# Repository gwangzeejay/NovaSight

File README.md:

# NovaSight · Rev A P1

NovaSight là nguyên mẫu hỗ trợ người dùng gậy trắng. NovaChest đo phía trước và cảnh báo qua hai vai. NovaCane Clip gắn dưới tay cầm, có rung, đèn Xin đường và nút SOS. NovaApp là giao diện thử nghiệm tùy chọn cho Clip.

**Tài liệu chính** · [Cookbook NovaSight](COOKBOOK.md)

| Thư mục | Nội dung |
| --- | --- |
| [firmware](firmware/) | PlatformIO cho ESP32-S3 NovaChest và ESP32-C3 NovaCane Clip |
| [novaapp](novaapp/) | Ứng dụng web tĩnh tiếng Việt cho Clip qua BLE |
| [output/3d](output/3d/NovaSight-3D.html) | Lắp ráp 3D và mô phỏng sử dụng: nhân vật tóc trắng, băng mắt, áo đen tím; bối cảnh phố với cửa hàng và cây xanh |
| [hardware](hardware/) | Hai project KiCad P1, báo cáo ERC/DRC và lịch sử đi dây |
| [output/pcb-prototype](output/pcb-prototype/README.md) | Gerber, khoan và yêu cầu chế tạo bo mẫu |
| [output/pcb-review](output/pcb-review/README.md) | BOM/CPL, DXF, STEP và ghi chú kỹ thuật |
| [source_review](source_review/) | Mô tả sản phẩm, brief PCB và tài liệu tham chiếu |
| [tools](tools/) và [tests](tests/) | Kiểm tra CAD/CAM, logic firmware và giao thức NovaApp. `python -X utf8 tools/bom.py` gộp BOM P1, gán mã LCSC và kiểm tra tồn kho JLCPCB, kết quả ở `output/bom/p1` |

Chạy từ thư mục gốc sau khi đã cài PlatformIO, Python, KiCad 10 và Node.js. Nếu đường dẫn dự án có dấu tiếng Việt, `pio run` lỗi `.tmp: Invalid argument`. Đặt trước `PYTHONUTF8=1`, `PLATFORMIO_BUILD_DIR` và `PLATFORMIO_LIBDEPS_DIR` trỏ tới thư mục ASCII, như [Cookbook mục 3](COOKBOOK.md).

```powershell
pio run -d firmware
python tools/hardware.py
python tools/test_core.py
node --test tests/app_test.mjs
python -m http.server 8000 --bind 127.0.0.1 --directory novaapp
```

Mở [NovaApp trên localhost](http://localhost:8000) trong trình duyệt hỗ trợ Web Bluetooth. Cookbook có lệnh cho đường dẫn Windows chứa dấu, thứ tự cấp nguồn, nạp, hiệu chuẩn và kiểm thử trên mẫu.

Để xem mô phỏng, chạy `python -m http.server 8765 --bind 127.0.0.1` từ thư mục gốc rồi mở [NovaSight 3D](http://localhost:8765/output/3d/NovaSight-3D.html), chọn **Mô phỏng sử dụng**. Phím **5** hoặc nút **Cận cảnh nhân vật** mở góc nhìn nhân vật; **1–4** đổi các góc nhìn còn lại, **Space** chạy/dừng, **F** trình chiếu. Hình học nhân vật và bối cảnh được dựng trực tiếp trong HTML; Three.js vẫn tải qua CDN nên cần kết nối mạng khi mở lần đầu.

P1 dùng cho thử nghiệm kỹ thuật có giám sát. Hãy tiếp tục dùng gậy trắng và kỹ thuật định hướng, di chuyển (O&M). Các phép đo trên bo thật, hiệu năng phát hiện nguy cơ và độ tin cậy SOS cần được nghiệm thu trước thử nghiệm di chuyển.

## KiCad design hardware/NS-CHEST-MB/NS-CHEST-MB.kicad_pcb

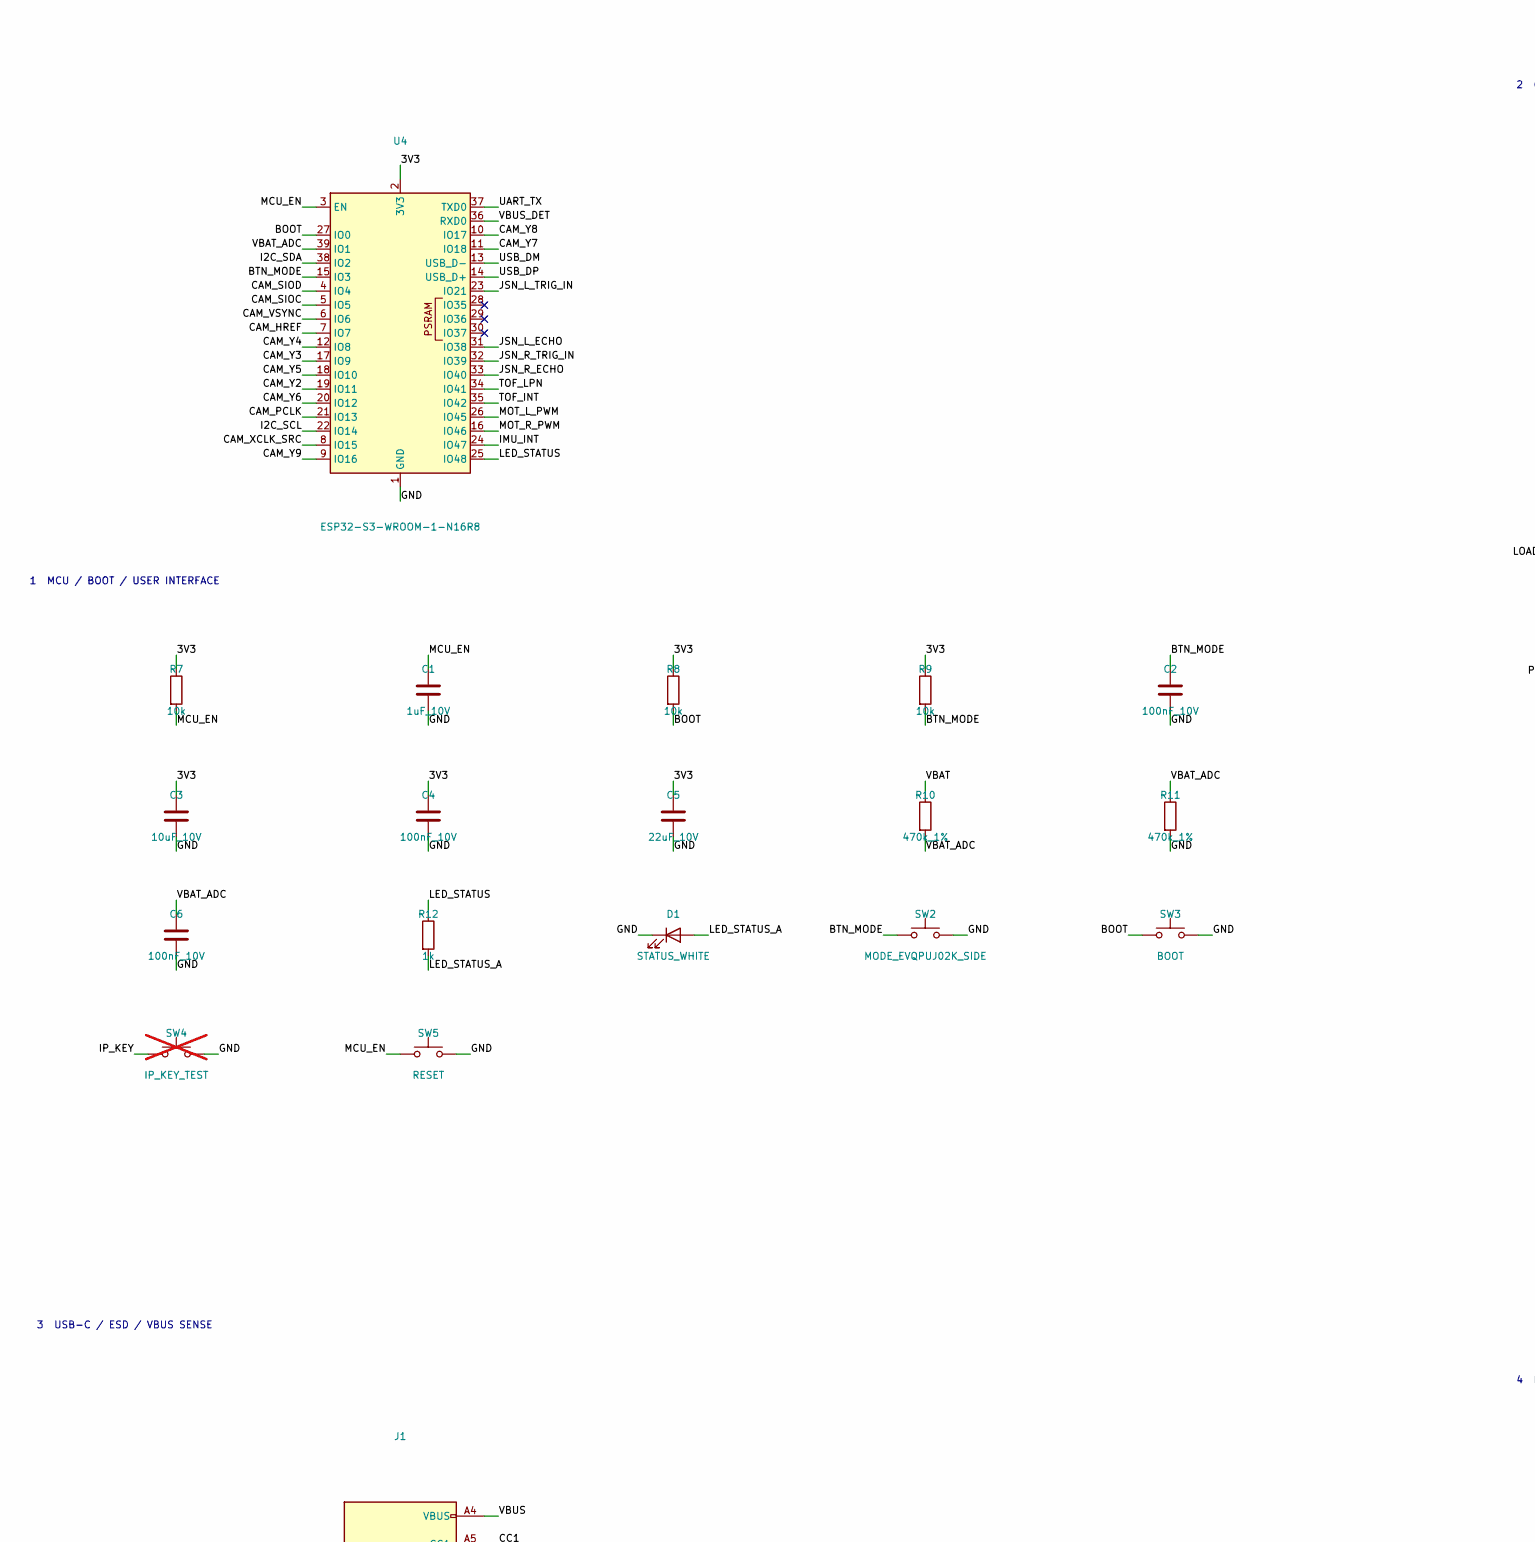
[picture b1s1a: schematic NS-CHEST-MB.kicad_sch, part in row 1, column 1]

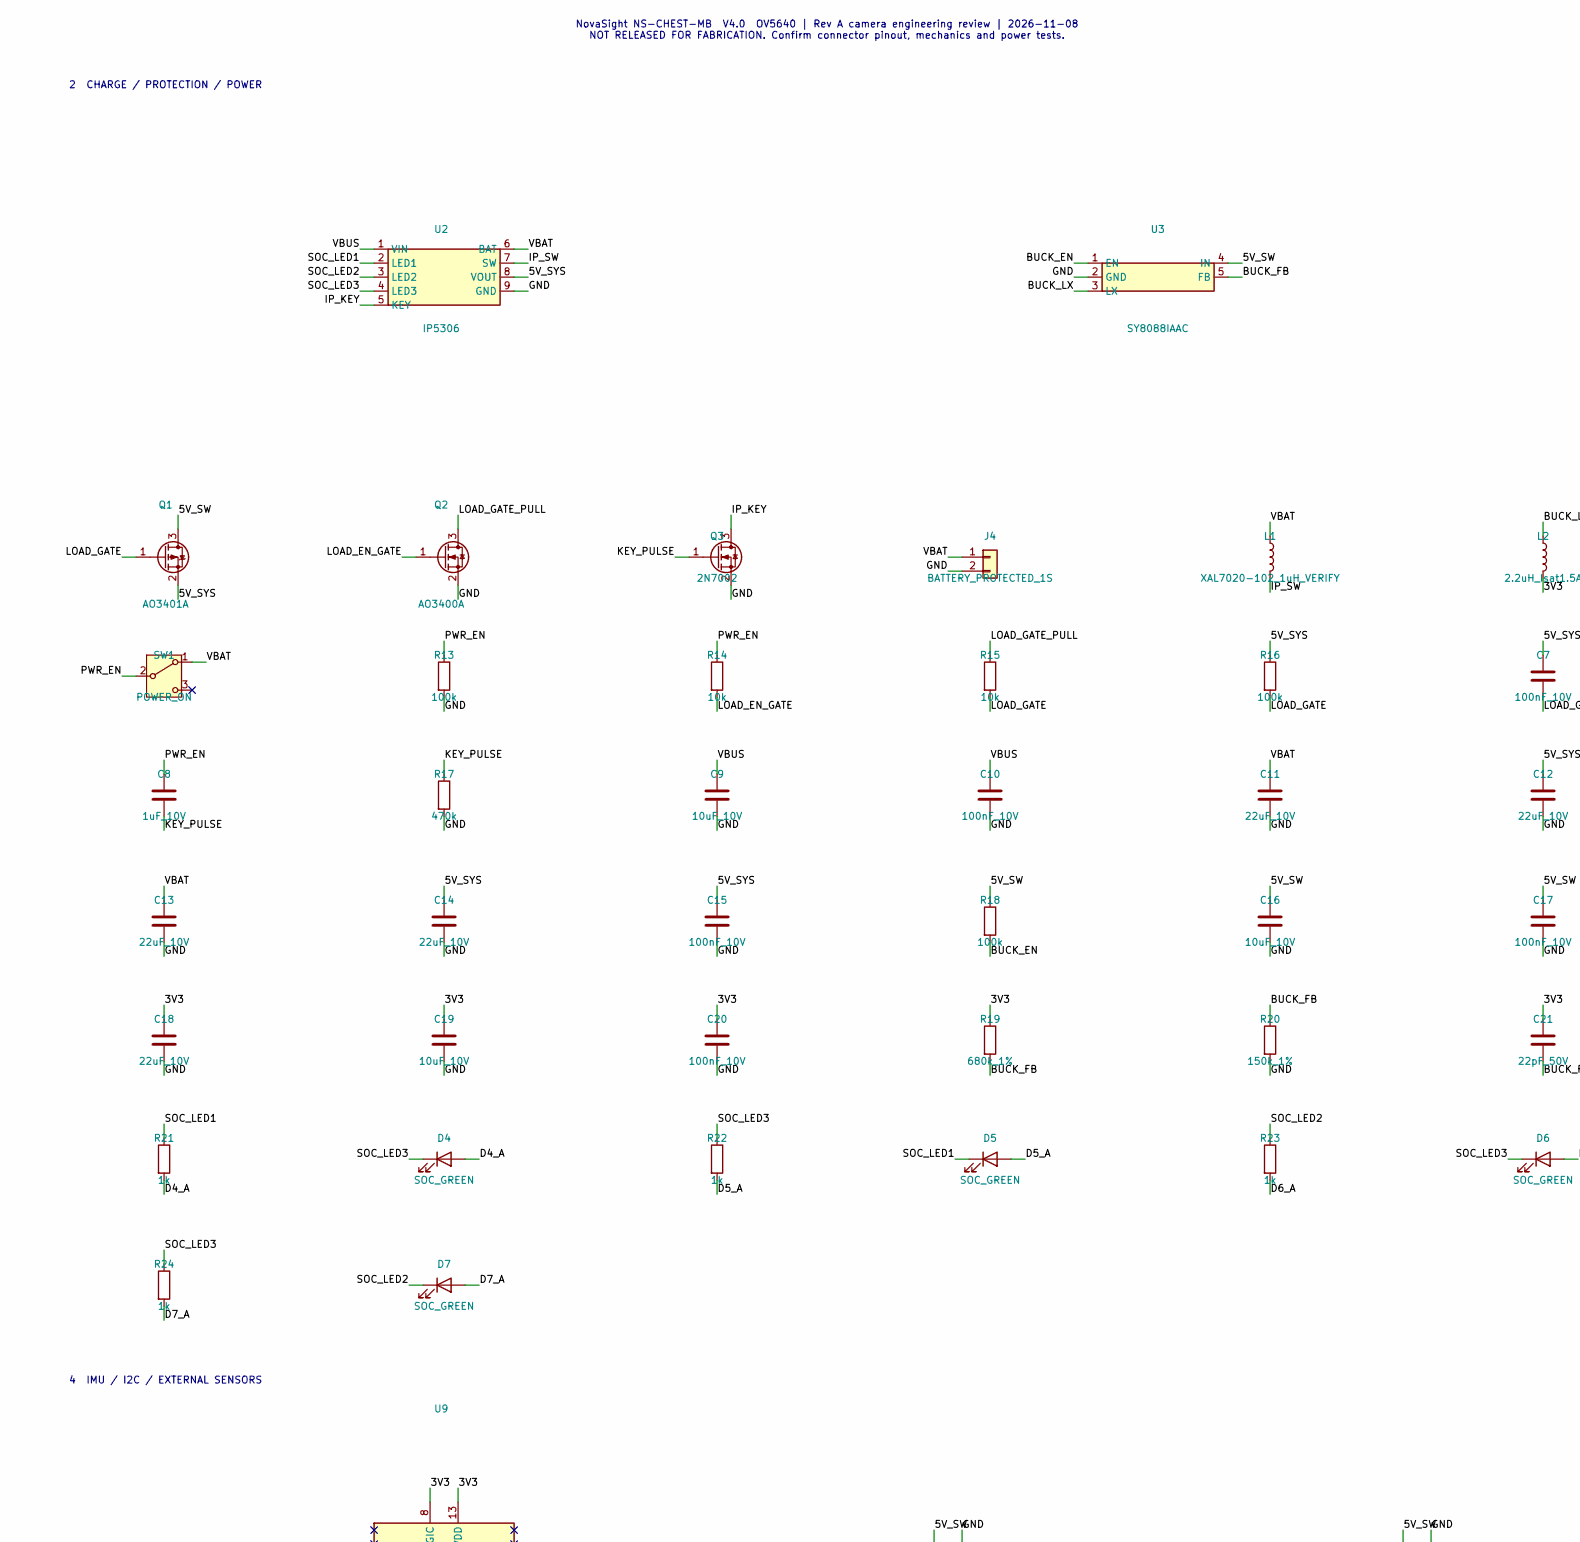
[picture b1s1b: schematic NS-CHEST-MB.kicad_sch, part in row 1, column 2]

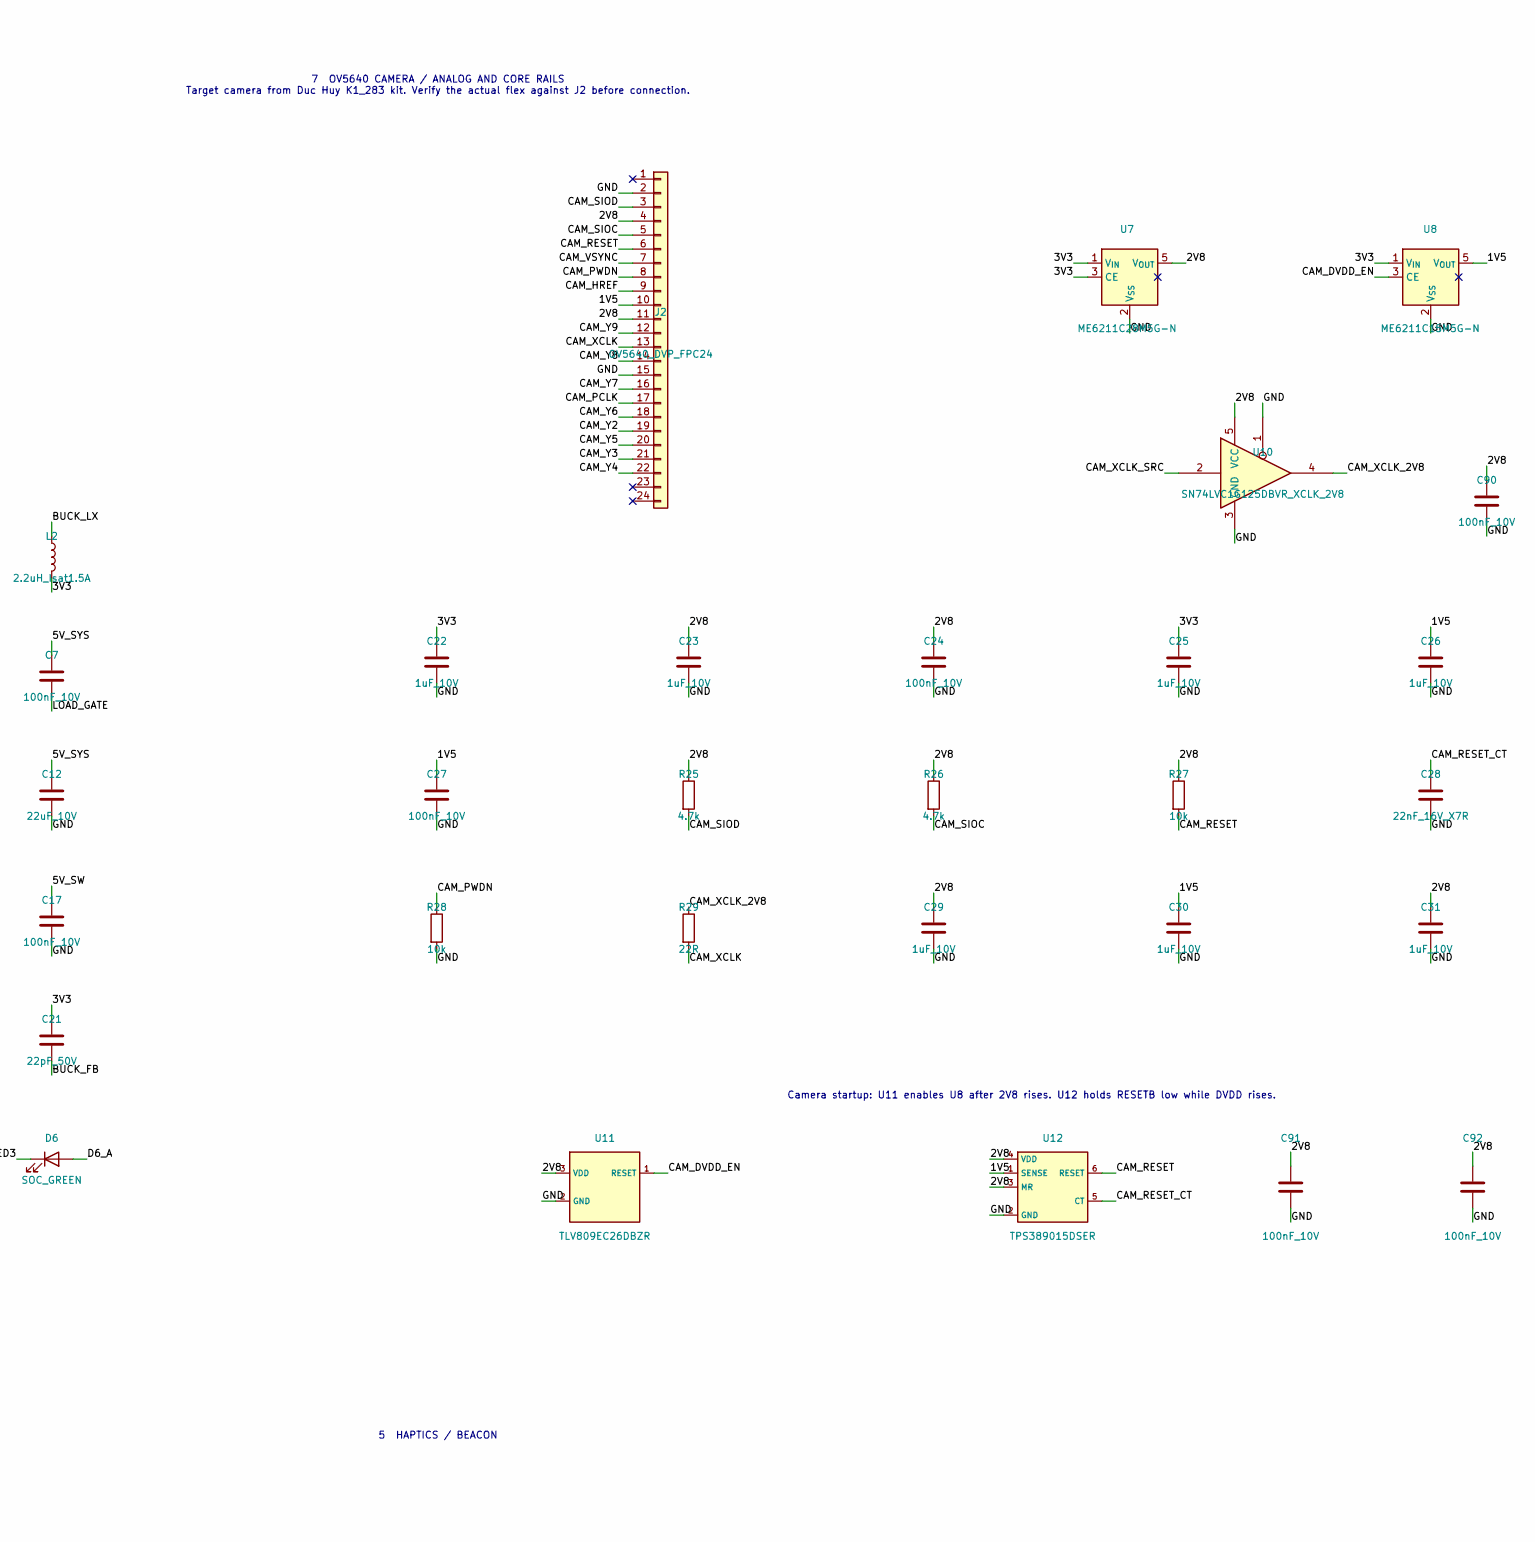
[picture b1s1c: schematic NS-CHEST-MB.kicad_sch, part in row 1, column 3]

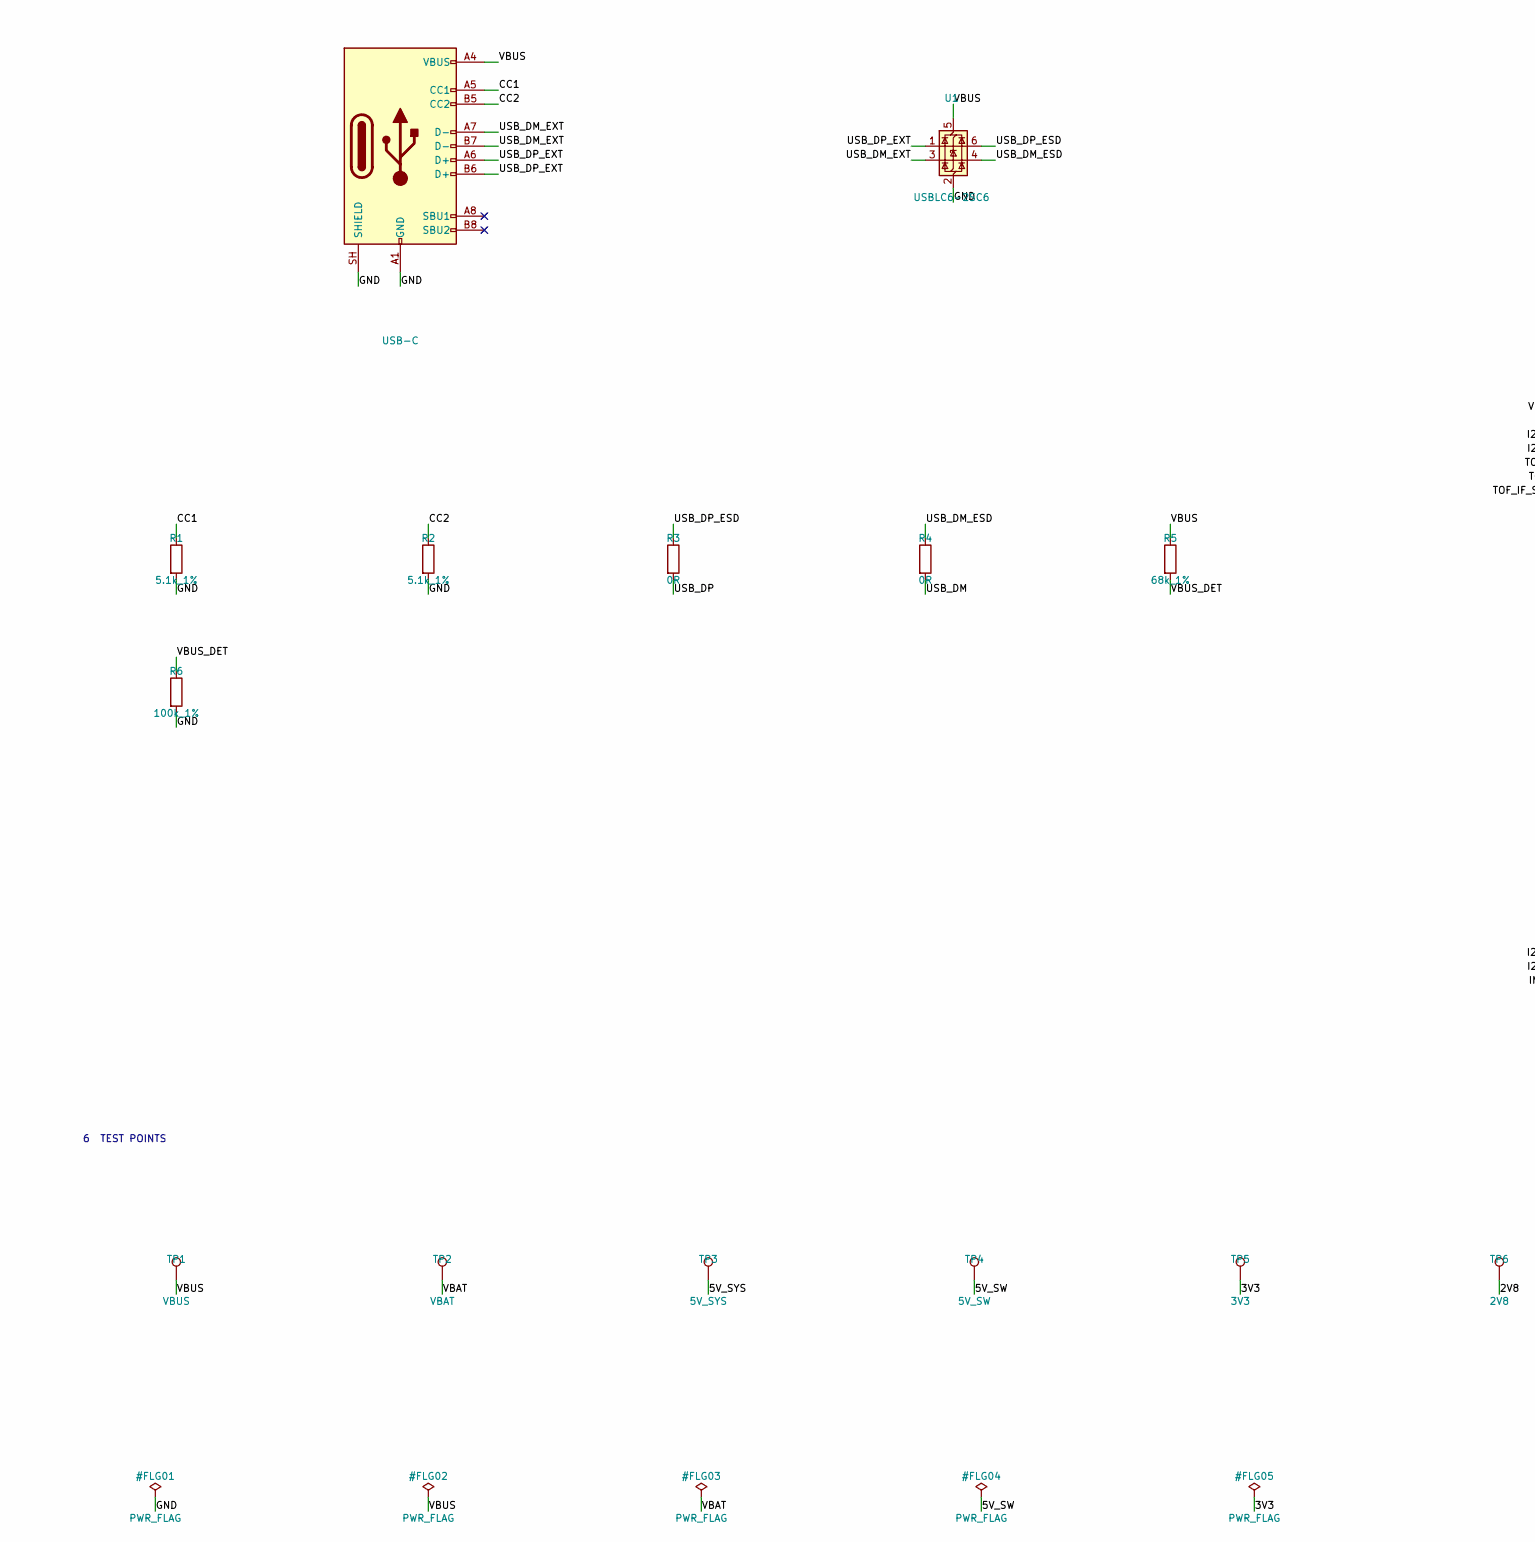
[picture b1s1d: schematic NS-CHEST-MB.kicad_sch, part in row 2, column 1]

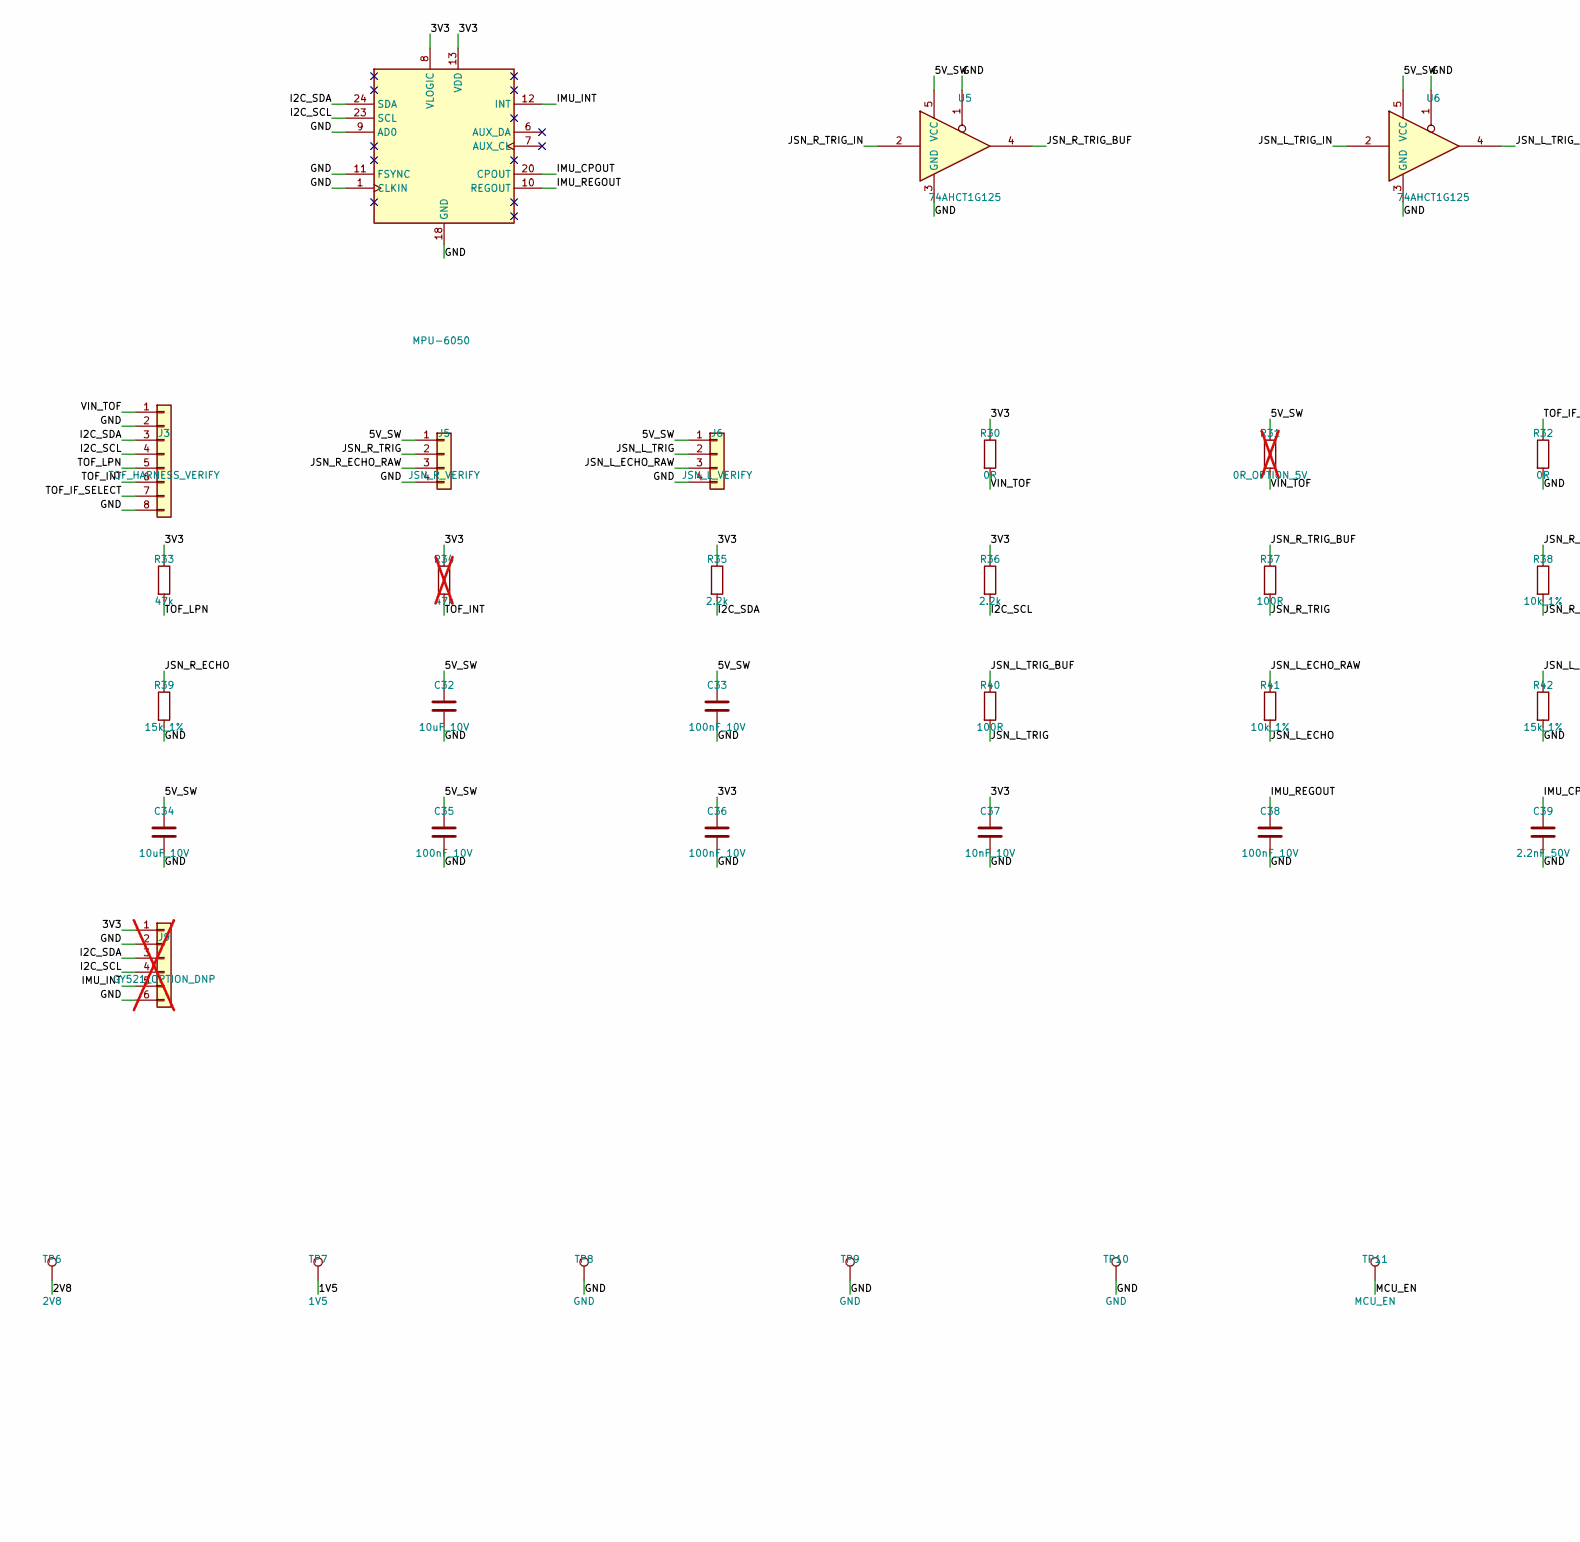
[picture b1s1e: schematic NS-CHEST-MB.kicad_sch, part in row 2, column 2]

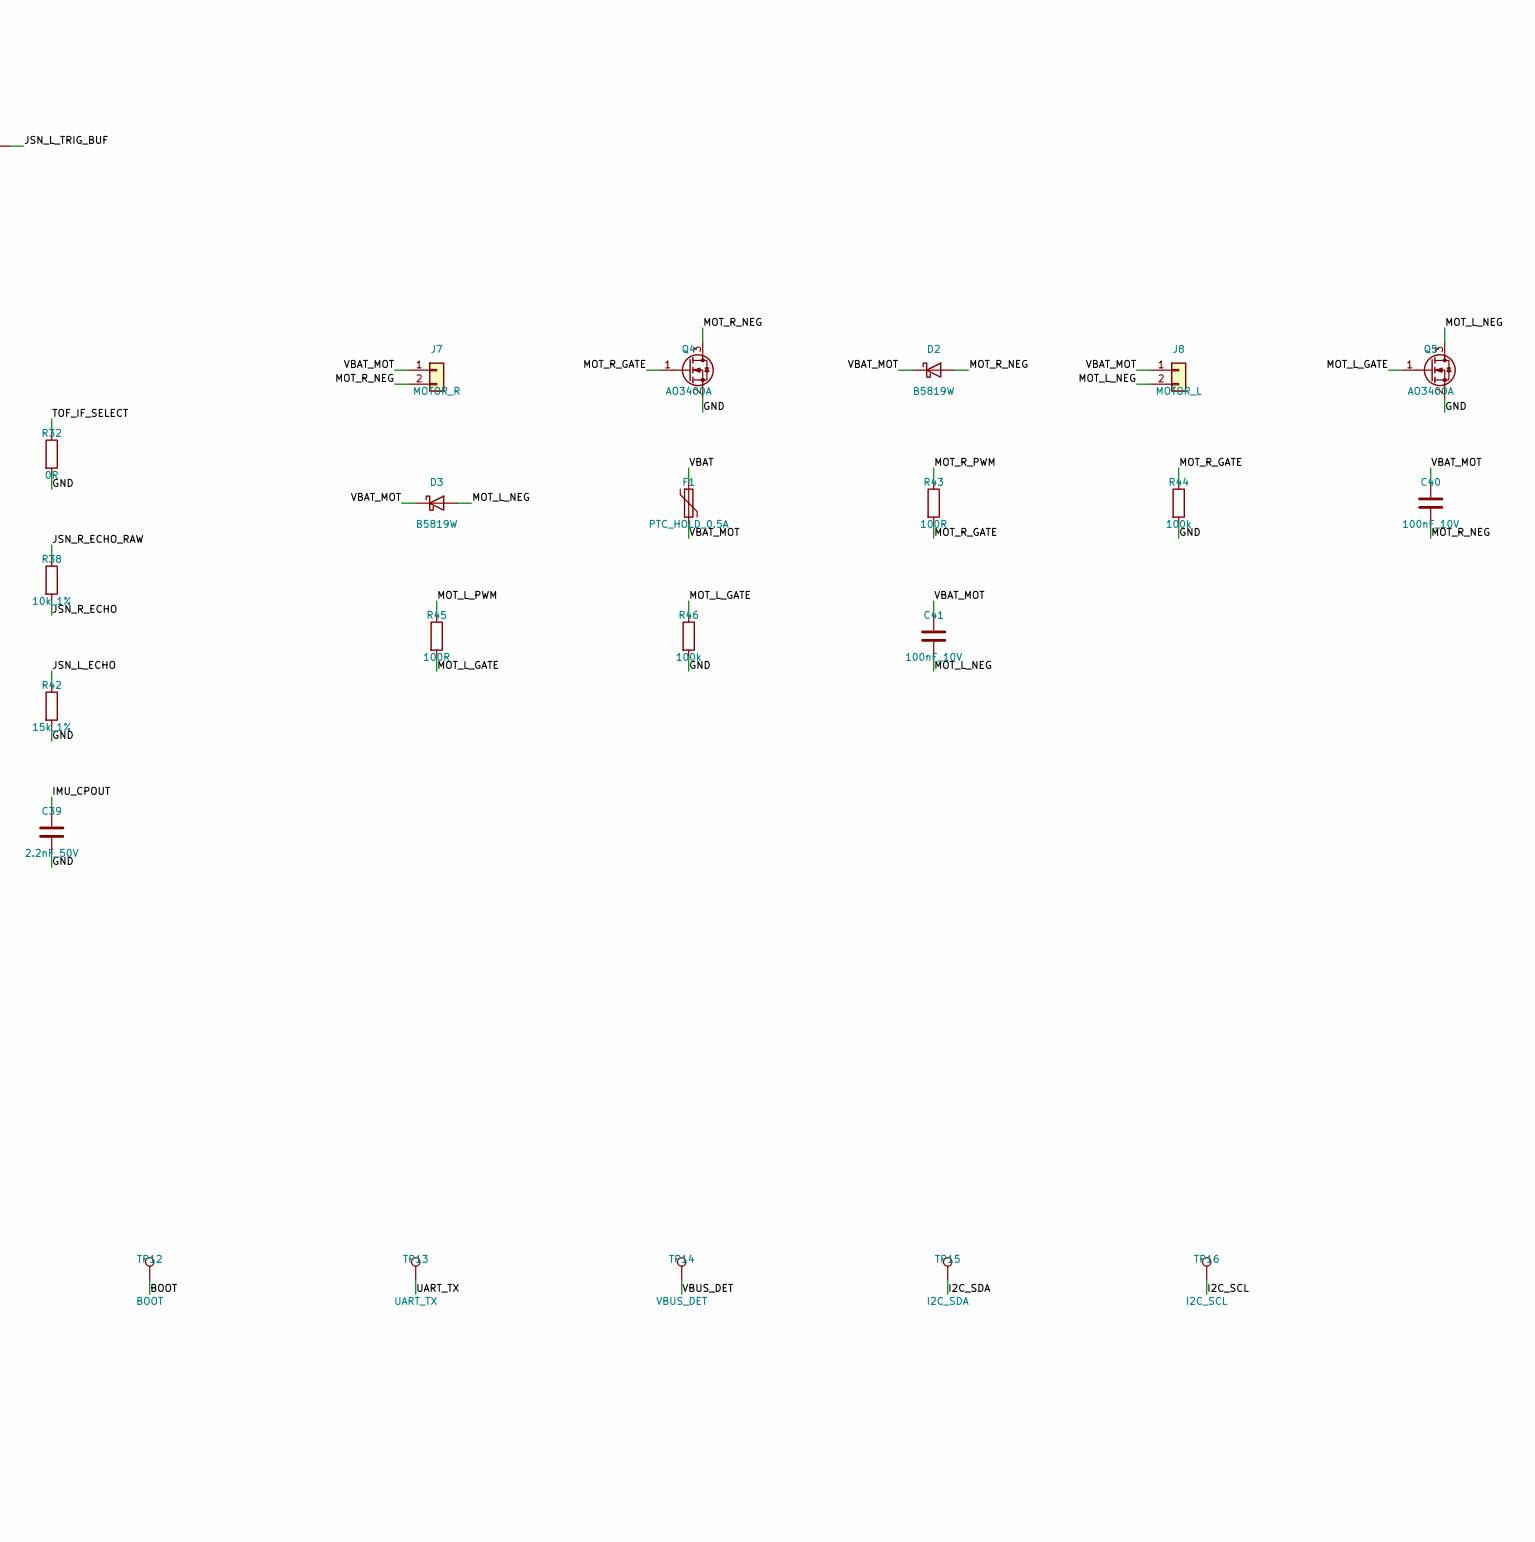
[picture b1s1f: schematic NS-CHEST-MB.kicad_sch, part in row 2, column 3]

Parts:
C1, C8, C22, C23, C25, C26, C29, C30, C31: 1uF_10V; C_0402_1005Metric
C2, C4, C6, C7, C10, C15, C17, C20, C24, C27, C33, C35, C36, C38, C40, C41, C90, C91, C92: 100nF_10V; C_0402_1005Metric
C3, C9, C16, C19, C32, C34: 10uF_10V; C_0603_1608Metric
C5, C11, C12, C13, C14, C18: 22uF_10V; C_0805_2012Metric
C21: 22pF_50V; C_0402_1005Metric
C28: 22nF_16V_X7R; C_0402_1005Metric
C37: 10nF_10V; C_0402_1005Metric
C39: 2.2nF_50V; C_0402_1005Metric
D1: STATUS_WHITE; LED_0603_1608Metric
D2, D3: B5819W; D_SOD-123
D4, D5, D6, D7: SOC_GREEN; LED_0603_1608Metric
F1: PTC_HOLD_0.5A; Fuse_1206_3216Metric
J1: USB-C; USB_C_Receptacle_GCT_USB4105-xx-A_16P_TopMnt_Horizontal
J2: OV5640_DVP_FPC24; Hirose_FH12-24S-0.5SH_1x24-1MP_P0.50mm_Horizontal
J3: TOF_HARNESS_VERIFY; JST_SH_SM08B-SRSS-TB_1x08-1MP_P1.00mm_Horizontal
J4: BATTERY_PROTECTED_1S; JST_PH_B2B-PH-K_1x02_P2.00mm_Vertical
J5: JSN_R_VERIFY; JST_PH_B4B-PH-K_1x04_P2.00mm_Vertical
J6: JSN_L_VERIFY; JST_PH_B4B-PH-K_1x04_P2.00mm_Vertical
J7: MOTOR_R; JST_PH_B2B-PH-K_1x02_P2.00mm_Vertical
J8: MOTOR_L; JST_PH_B2B-PH-K_1x02_P2.00mm_Vertical
J9: GY521_OPTION_DNP; JST_SH_SM06B-SRSS-TB_1x06-1MP_P1.00mm_Horizontal; not fitted
L1: XAL7020-102_1uH_VERIFY; L_Coilcraft_XAL7020-102
L2: 2.2uH_Isat1.5A; L_Bourns-SRN4018
Q1: AO3401A; SOT-23
Q2, Q4, Q5: AO3400A; SOT-23
Q3: 2N7002; SOT-23
R1, R2: 5.1k_1%; R_0402_1005Metric
R3, R4, R30, R32: 0R; R_0402_1005Metric
R5: 68k_1%; R_0402_1005Metric
R6: 100k_1%; R_0402_1005Metric
R7, R8, R9, R14, R15, R27, R28: 10k; R_0402_1005Metric
R10, R11: 470k_1%; R_0402_1005Metric
R12, R21, R22, R23, R24: 1k; R_0402_1005Metric
R13, R16, R18, R44, R46: 100k; R_0402_1005Metric
R17: 470k; R_0402_1005Metric
R19: 680k_1%; R_0402_1005Metric
R20: 150k_1%; R_0402_1005Metric
R25, R26: 4.7k; R_0402_1005Metric
R29: 22R; R_0402_1005Metric
R31: 0R_OPTION_5V; R_0402_1005Metric; not fitted
R33: 47k; R_0402_1005Metric
R34: 47k; R_0402_1005Metric; not fitted
R35, R36: 2.2k; R_0402_1005Metric
R37, R40, R43, R45: 100R; R_0402_1005Metric
R38, R41: 10k_1%; R_0402_1005Metric
R39, R42: 15k_1%; R_0402_1005Metric
SW1: POWER_ON; SW_SPDT_Shouhan_MSK12C02
SW2: MODE_EVQPUJ02K_SIDE; Panasonic_EVQPUJ_EVQPUA
SW3: BOOT; SW_SPST_TL3342
SW4: IP_KEY_TEST; SW_SPST_TL3342; not fitted
SW5: RESET; SW_SPST_TL3342
TP1: VBUS; TestPoint_Pad_D1.0mm
TP2: VBAT; TestPoint_Pad_D1.0mm
TP3: 5V_SYS; TestPoint_Pad_D1.0mm
TP4: 5V_SW; TestPoint_Pad_D1.0mm
TP5: 3V3; TestPoint_Pad_D1.0mm
TP6: 2V8; TestPoint_Pad_D1.0mm
TP7: 1V5; TestPoint_Pad_D1.0mm
TP8, TP9, TP10: GND; TestPoint_Pad_D1.0mm
TP11: MCU_EN; TestPoint_Pad_D1.0mm
TP12: BOOT; TestPoint_Pad_D1.0mm
TP13: UART_TX; TestPoint_Pad_D1.0mm
TP14: VBUS_DET; TestPoint_Pad_D1.0mm
TP15: I2C_SDA; TestPoint_Pad_D1.0mm
TP16: I2C_SCL; TestPoint_Pad_D1.0mm
U1: USBLC6-2SC6; SOT-23-6
U2: IP5306; HSOP-8-1EP_3.9x4.9mm_P1.27mm_EP2.41x3.1mm
U3: SY8088IAAC; SOT-23-5; LCSC C479072
U4: ESP32-S3-WROOM-1-N16R8; ESP32-S3-WROOM-1
U5, U6: 74AHCT1G125; SOT-23-5
U7: ME6211C28M5G-N; SOT-23-5
U8: ME6211C15M5G-N; SOT-23-5
U9: MPU-6050; InvenSense_QFN-24_4x4mm_P0.5mm; LCSC C24112
U10: SN74LVC1G125DBVR_XCLK_2V8; SOT-23-5
U11: TLV809EC26DBZR; SOT-23
U12: TPS389015DSER; WSON-6_1.5x1.5mm_P0.5mm

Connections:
/1V5: C26.1, C27.1, C30.1, J2.10, TP7.1, U8.5 (V_{OUT}), U12.1 (SENSE)
/2V8: C23.1, C24.1, C29.1, C31.1, C90.1, C91.1, C92.1, J2.4, J2.11, R25.1, R26.1, R27.1, TP6.1, U7.5 (V_{OUT}), U10.5 (VCC), U11.3 (VDD), U12.3 (MR), U12.4 (VDD)
/3V3: C3.1, C4.1, C5.1, C18.1, C19.1, C20.1, C21.1, C22.1, C25.1, C36.1, C37.1, J9.1, L2.2, R7.1, R8.1, R9.1, R19.1, R30.1, R33.1, R34.1, R35.1, R36.1, TP5.1, U4.2 (3V3), U7.1 (V_{IN}), U7.3 (CE), U8.1 (V_{IN}), U9.8 (VLOGIC), U9.13 (VDD)
/5V_SW: C16.1, C17.1, C32.1, C33.1, C34.1, C35.1, J5.1, J6.1, Q1.3 (D), R18.1, R31.1, TP4.1, U3.4 (IN), U5.5 (VCC), U6.5 (VCC)
/5V_SYS: C7.1, C12.1, C14.1, C15.1, Q1.2 (S), R16.1, TP3.1, U2.8 (VOUT)
/BOOT: R8.2, SW3.1, TP12.1, U4.27 (IO0)
/BTN_MODE: C2.1, R9.2, SW2.1, U4.15 (IO3)
/BUCK_EN: R18.2, U3.1 (EN)
/BUCK_FB: C21.2, R19.2, R20.1, U3.5 (FB)
/BUCK_LX: L2.1, U3.3 (LX)
/CAM_DVDD_EN: U8.3 (CE), U11.1 (RESET)
/CAM_HREF: J2.9, U4.7 (IO7)
/CAM_PCLK: J2.17, U4.21 (IO13)
/CAM_PWDN: J2.8, R28.1
/CAM_RESET: J2.6, R27.2, U12.6 (RESET)
/CAM_RESET_CT: C28.1, U12.5 (CT)
/CAM_SIOC: J2.5, R26.2, U4.5 (IO5)
/CAM_SIOD: J2.3, R25.2, U4.4 (IO4)
/CAM_VSYNC: J2.7, U4.6 (IO6)
/CAM_XCLK: J2.13, R29.2
/CAM_XCLK_2V8: R29.1, U10.4
/CAM_XCLK_SRC: U4.8 (IO15), U10.2
/CAM_Y2: J2.19, U4.19 (IO11)
/CAM_Y3: J2.21, U4.17 (IO9)
/CAM_Y4: J2.22, U4.12 (IO8)
/CAM_Y5: J2.20, U4.18 (IO10)
/CAM_Y6: J2.18, U4.20 (IO12)
/CAM_Y7: J2.16, U4.11 (IO18)
/CAM_Y8: J2.14, U4.10 (IO17)
/CAM_Y9: J2.12, U4.9 (IO16)
/CC1: J1.A5 (CC1), R1.1
/CC2: J1.B5 (CC2), R2.1
/D4_A: D4.2 (A), R21.2
/D5_A: D5.2 (A), R22.2
/D6_A: D6.2 (A), R23.2
/D7_A: D7.2 (A), R24.2
/GND: C1.2, C2.2, C3.2, C4.2, C5.2, C6.2, C9.2, C10.2, C11.2, C12.2, C13.2, C14.2, C15.2, C16.2, C17.2, C18.2, C19.2, C20.2, C22.2, C23.2, C24.2, C25.2, C26.2, C27.2, C28.2, C29.2, C30.2, C31.2, C32.2, C33.2, C34.2, C35.2, C36.2, C37.2, C38.2, C39.2, C90.2, C91.2, C92.2, D1.1 (K), J1.A1 (GND), J1.A12 (GND), J1.B1 (GND), J1.B12 (GND), J1.SH (SHIELD), J2.2, J2.15, J3.2, J3.8, J4.2, J5.4, J6.4, J9.2, J9.6, Q2.2 (S), Q3.2 (S), Q4.2 (S), Q5.2 (S), R1.2, R2.2, R6.2, R11.2, R13.2, R17.2, R20.2, R28.2, R32.2, R39.2, R42.2, R44.2, R46.2, SW2.2, SW3.2, SW4.2, SW5.2, TP8.1, TP9.1, TP10.1, U1.2 (GND), U2.9 (GND), U3.2 (GND), U4.1 (GND), U4.40 (GND), U4.41 (GND), U5.1, U5.3 (GND), U6.1, U6.3 (GND), U7.2 (V_{SS}), U8.2 (V_{SS}), U9.1 (CLKIN), U9.9 (AD0), U9.11 (FSYNC), U9.18 (GND), U10.1, U10.3 (GND), U11.2 (GND), U12.2 (GND)
/I2C_SCL: J3.4, J9.4, R36.2, TP16.1, U4.22 (IO14), U9.23 (SCL)
/I2C_SDA: J3.3, J9.3, R35.2, TP15.1, U4.38 (IO2), U9.24 (SDA)
/IMU_CPOUT: C39.1, U9.20 (CPOUT)
/IMU_INT: J9.5, U4.24 (IO47), U9.12 (INT)
/IMU_REGOUT: C38.1, U9.10 (REGOUT)
/IP_KEY: Q3.3 (D), SW4.1, U2.5 (KEY)
/IP_SW: L1.2, U2.7 (SW)
/JSN_L_ECHO: R41.2, R42.1, U4.31 (IO38)
/JSN_L_ECHO_RAW: J6.3, R41.1
/JSN_L_TRIG: J6.2, R40.2
/JSN_L_TRIG_BUF: R40.1, U6.4
/JSN_L_TRIG_IN: U4.23 (IO21), U6.2
/JSN_R_ECHO: R38.2, R39.1, U4.33 (IO40)
/JSN_R_ECHO_RAW: J5.3, R38.1
/JSN_R_TRIG: J5.2, R37.2
/JSN_R_TRIG_BUF: R37.1, U5.4
/JSN_R_TRIG_IN: U4.32 (IO39), U5.2
/KEY_PULSE: C8.2, Q3.1 (G), R17.1
/LED_STATUS: R12.1, U4.25 (IO48)
/LED_STATUS_A: D1.2 (A), R12.2
/LOAD_EN_GATE: Q2.1 (G), R14.2
/LOAD_GATE: C7.2, Q1.1 (G), R15.2, R16.2
/LOAD_GATE_PULL: Q2.3 (D), R15.1
/MCU_EN: C1.1, R7.2, SW5.1, TP11.1, U4.3 (EN)
/MOT_L_GATE: Q5.1 (G), R45.2, R46.1
/MOT_L_NEG: C41.2, D3.2 (A), J8.2, Q5.3 (D)
/MOT_L_PWM: R45.1, U4.26 (IO45)
/MOT_R_GATE: Q4.1 (G), R43.2, R44.1
/MOT_R_NEG: C40.2, D2.2 (A), J7.2, Q4.3 (D)
/MOT_R_PWM: R43.1, U4.16 (IO46)
/PWR_EN: C8.1, R13.1, R14.1, SW1.2 (B)
/SOC_LED1: D5.1 (K), R21.1, U2.2 (LED1)
/SOC_LED2: D7.1 (K), R23.1, U2.3 (LED2)
/SOC_LED3: D4.1 (K), D6.1 (K), R22.1, R24.1, U2.4 (LED3)
/TOF_IF_SELECT: J3.7, R32.1
/TOF_INT: J3.6, R34.2, U4.35 (IO42)
/TOF_LPN: J3.5, R33.2, U4.34 (IO41)
/UART_TX: TP13.1, U4.37 (TXD0)
/USB_DM: R4.2, U4.13 (USB_D-)
/USB_DM_ESD: R4.1, U1.4 (I/O2)
/USB_DM_EXT: J1.A7 (D-), J1.B7 (D-), U1.3 (I/O2)
/USB_DP: R3.2, U4.14 (USB_D+)
/USB_DP_ESD: R3.1, U1.6 (I/O1)
/USB_DP_EXT: J1.A6 (D+), J1.B6 (D+), U1.1 (I/O1)
/VBAT: C11.1, C13.1, F1.1, J4.1, L1.1, R10.1, SW1.1 (A), TP2.1, U2.6 (BAT)
/VBAT_ADC: C6.1, R10.2, R11.1, U4.39 (IO1)
/VBAT_MOT: C40.1, C41.1, D2.1 (K), D3.1 (K), F1.2, J7.1, J8.1
/VBUS: C9.1, C10.1, J1.A4 (VBUS), J1.A9 (VBUS), J1.B4 (VBUS), J1.B9 (VBUS), R5.1, TP1.1, U1.5 (VBUS), U2.1 (VIN)
/VBUS_DET: R5.2, R6.1, TP14.1, U4.36 (RXD0)
/VIN_TOF: J3.1, R30.2, R31.2

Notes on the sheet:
1 MCU / BOOT / USER INTERFACE
2 CHARGE / PROTECTION / POWER
3 USB-C / ESD / VBUS SENSE
4 IMU / I2C / EXTERNAL SENSORS
5 HAPTICS / BEACON
6 TEST POINTS
7 OV5640 CAMERA / ANALOG AND CORE RAILS Target camera from Duc Huy K1_283 kit. Verify the actual flex against J2 before connection.
NovaSight NS-CHEST-MB V4.0 OV5640 | Rev A camera engineering review | 2026-11-08 NOT RELEASED FOR FABRICATION. Confirm connector pinout, mechanics and power tests.
Camera startup: U11 enables U8 after 2V8 rises. U12 holds RESETB low while DVDD rises.
